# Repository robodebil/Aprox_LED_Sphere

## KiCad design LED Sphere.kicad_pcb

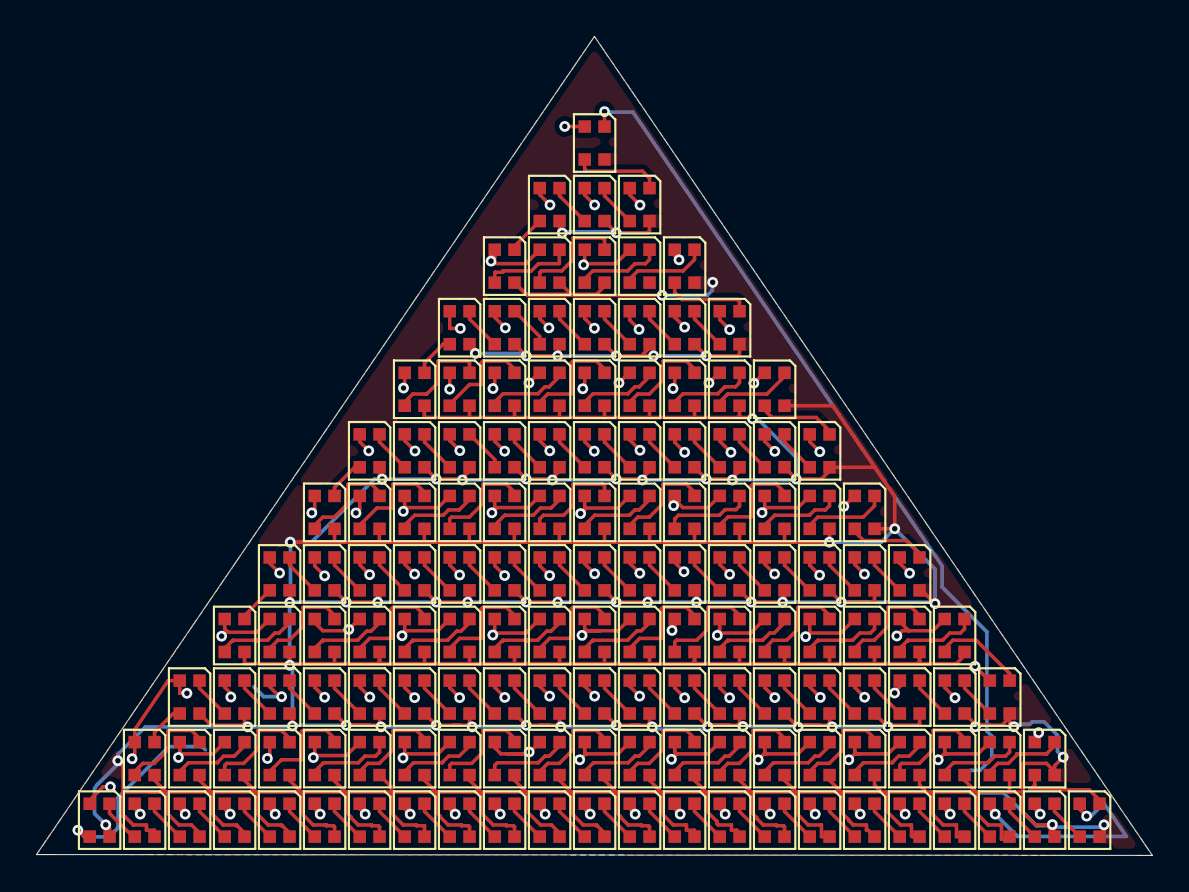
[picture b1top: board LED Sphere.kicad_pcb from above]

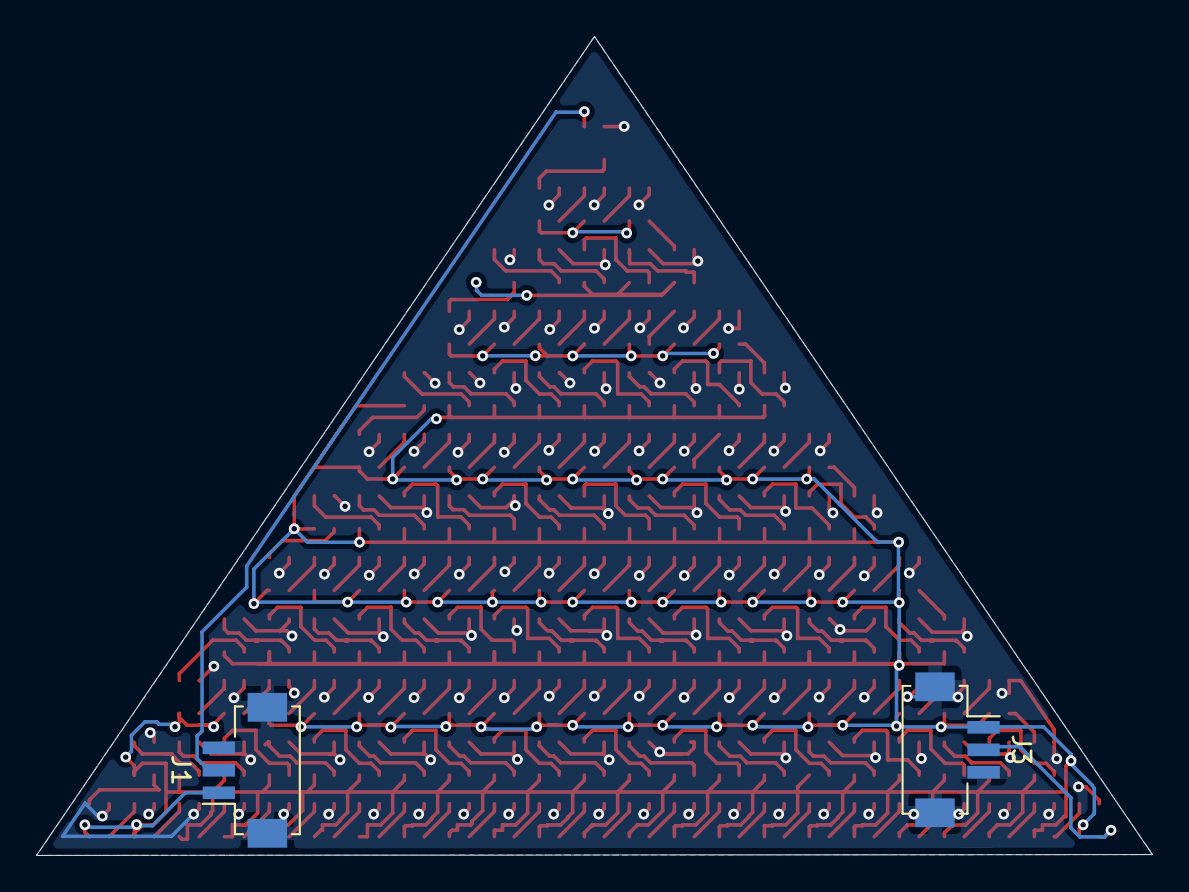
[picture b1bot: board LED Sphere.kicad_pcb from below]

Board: 2 copper layers, 62.0 x 45.5 mm, 146 parts (2 on the bottom side), 147 nets.

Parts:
D1, D2, D3, D4, D5, D6, D7, D8, D9, D10, D11, D12, D13, D14, D15, D16, D17, D18, D19, D20, D21, D22, D23, D24, D25, D26, D27, D28, D29, D30, D31, D32, D33, D34, D35, D36, D37, D38, D39, D40, D41, D42, D43, D44, D45, D46, D47, D48, D49, D50, D51, D52, D53, D54, D55, D56, D57, D58, D59, D60, D61, D62, D63, D64, D65, D66, D67, D68, D69, D70, D71, D72, D73, D74, D75, D76, D77, D78, D79, D80, D81, D82, D83, D84, D85, D86, D87, D88, D89, D90, D91, D92, D93, D94, D95, D96, D97, D98, D99, D100, D101, D102, D103, D104, D105, D106, D107, D108, D109, D110, D111, D112, D113, D114, D115, D116, D117, D118, D119, D120, D121, D122, D123, D124, D125, D126, D127, D128, D129, D130, D131, D132, D133, D134, D135, D136, D137, D138, D139, D140, D141, D142, D143, D144: WS2812B-2020; LED_WS2812B-2020_PLCC4_2.0x2.0mm
J1, J3: Conn_01x03_MountingPin; Hirose_DF13C_CL535-0403-5-51_1x03-1MP_P1.25mm_Vertical

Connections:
+5V: D1.2 (VSS), D2.2 (VSS), D3.2 (VSS), D4.2 (VSS), D5.2 (VSS), D6.2 (VSS), D7.2 (VSS), D8.2 (VSS), D9.2 (VSS), D10.2 (VSS), D11.2 (VSS), D12.2 (VSS), D13.2 (VSS), D14.2 (VSS), D15.2 (VSS), D16.2 (VSS), D17.2 (VSS), D18.2 (VSS), D19.2 (VSS), D20.2 (VSS), D21.2 (VSS), D22.2 (VSS), D23.2 (VSS), D24.2 (VSS), D25.2 (VSS), D26.2 (VSS), D27.2 (VSS), D28.2 (VSS), D29.2 (VSS), D30.2 (VSS), D31.2 (VSS), D32.2 (VSS), D33.2 (VSS), D34.2 (VSS), D35.2 (VSS), D36.2 (VSS), D37.2 (VSS), D38.2 (VSS), D39.2 (VSS), D40.2 (VSS), D41.2 (VSS), D42.2 (VSS), D43.2 (VSS), D44.2 (VSS), D45.2 (VSS), D46.2 (VSS), D47.2 (VSS), D48.2 (VSS), D49.2 (VSS), D50.2 (VSS), D51.2 (VSS), D52.2 (VSS), D53.2 (VSS), D54.2 (VSS), D55.2 (VSS), D56.2 (VSS), D57.2 (VSS), D58.2 (VSS), D59.2 (VSS), D60.2 (VSS), D61.2 (VSS), D62.2 (VSS), D63.2 (VSS), D64.2 (VSS), D65.2 (VSS), D66.2 (VSS), D67.2 (VSS), D68.2 (VSS), D69.2 (VSS), D70.2 (VSS), D71.2 (VSS), D72.2 (VSS), D73.2 (VSS), D74.2 (VSS), D75.2 (VSS), D76.2 (VSS), D77.2 (VSS), D78.2 (VSS), D79.2 (VSS), D80.2 (VSS), D81.2 (VSS), D82.2 (VSS), D83.2 (VSS), D84.2 (VSS), D85.2 (VSS), D86.2 (VSS), D87.2 (VSS), D88.2 (VSS), D89.2 (VSS), D90.2 (VSS), D91.2 (VSS), D92.2 (VSS), D93.2 (VSS), D94.2 (VSS), D95.2 (VSS), D96.2 (VSS), D97.2 (VSS), D98.2 (VSS), D99.2 (VSS), D100.2 (VSS), D101.2 (VSS), D102.2 (VSS), D103.2 (VSS), D104.2 (VSS), D105.2 (VSS), D106.2 (VSS), D107.2 (VSS), D108.2 (VSS), D109.2 (VSS), D110.2 (VSS), D111.2 (VSS), D112.2 (VSS), D113.2 (VSS), D114.2 (VSS), D115.2 (VSS), D116.2 (VSS), D117.2 (VSS), D118.2 (VSS), D119.2 (VSS), D120.2 (VSS), D121.2 (VSS), D122.2 (VSS), D123.2 (VSS), D124.2 (VSS), D125.2 (VSS), D126.2 (VSS), D127.2 (VSS), D128.2 (VSS), D129.2 (VSS), D130.2 (VSS), D131.2 (VSS), D132.2 (VSS), D133.2 (VSS), D134.2 (VSS), D135.2 (VSS), D136.2 (VSS), D137.2 (VSS), D138.2 (VSS), D139.2 (VSS), D140.2 (VSS), D141.2 (VSS), D142.2 (VSS), D143.2 (VSS), D144.2 (VSS), J1.3, J1.MP (MountPin), J3.3, J3.MP (MountPin)
/DATA_IN: D1.3 (DIN), J3.2
/DATA_OUT: D144.1 (DOUT), J1.2
GND: D1.4 (VDD), D2.4 (VDD), D3.4 (VDD), D4.4 (VDD), D5.4 (VDD), D6.4 (VDD), D7.4 (VDD), D8.4 (VDD), D9.4 (VDD), D10.4 (VDD), D11.4 (VDD), D12.4 (VDD), D13.4 (VDD), D14.4 (VDD), D15.4 (VDD), D16.4 (VDD), D17.4 (VDD), D18.4 (VDD), D19.4 (VDD), D20.4 (VDD), D21.4 (VDD), D22.4 (VDD), D23.4 (VDD), D24.4 (VDD), D25.4 (VDD), D26.4 (VDD), D27.4 (VDD), D28.4 (VDD), D29.4 (VDD), D30.4 (VDD), D31.4 (VDD), D32.4 (VDD), D33.4 (VDD), D34.4 (VDD), D35.4 (VDD), D36.4 (VDD), D37.4 (VDD), D38.4 (VDD), D39.4 (VDD), D40.4 (VDD), D41.4 (VDD), D42.4 (VDD), D43.4 (VDD), D44.4 (VDD), D45.4 (VDD), D46.4 (VDD), D47.4 (VDD), D48.4 (VDD), D49.4 (VDD), D50.4 (VDD), D51.4 (VDD), D52.4 (VDD), D53.4 (VDD), D54.4 (VDD), D55.4 (VDD), D56.4 (VDD), D57.4 (VDD), D58.4 (VDD), D59.4 (VDD), D60.4 (VDD), D61.4 (VDD), D62.4 (VDD), D63.4 (VDD), D64.4 (VDD), D65.4 (VDD), D66.4 (VDD), D67.4 (VDD), D68.4 (VDD), D69.4 (VDD), D70.4 (VDD), D71.4 (VDD), D72.4 (VDD), D73.4 (VDD), D74.4 (VDD), D75.4 (VDD), D76.4 (VDD), D77.4 (VDD), D78.4 (VDD), D79.4 (VDD), D80.4 (VDD), D81.4 (VDD), D82.4 (VDD), D83.4 (VDD), D84.4 (VDD), D85.4 (VDD), D86.4 (VDD), D87.4 (VDD), D88.4 (VDD), D89.4 (VDD), D90.4 (VDD), D91.4 (VDD), D92.4 (VDD), D93.4 (VDD), D94.4 (VDD), D95.4 (VDD), D96.4 (VDD), D97.4 (VDD), D98.4 (VDD), D99.4 (VDD), D100.4 (VDD), D101.4 (VDD), D102.4 (VDD), D103.4 (VDD), D104.4 (VDD), D105.4 (VDD), D106.4 (VDD), D107.4 (VDD), D108.4 (VDD), D109.4 (VDD), D110.4 (VDD), D111.4 (VDD), D112.4 (VDD), D113.4 (VDD), D114.4 (VDD), D115.4 (VDD), D116.4 (VDD), D117.4 (VDD), D118.4 (VDD), D119.4 (VDD), D120.4 (VDD), D121.4 (VDD), D122.4 (VDD), D123.4 (VDD), D124.4 (VDD), D125.4 (VDD), D126.4 (VDD), D127.4 (VDD), D128.4 (VDD), D129.4 (VDD), D130.4 (VDD), D131.4 (VDD), D132.4 (VDD), D133.4 (VDD), D134.4 (VDD), D135.4 (VDD), D136.4 (VDD), D138.4 (VDD), D139.4 (VDD), D140.4 (VDD), D141.4 (VDD), D142.4 (VDD), D143.4 (VDD), D144.4 (VDD), J1.1, J3.1
unnamed: D1.1 (DOUT), D2.3 (DIN)
unnamed: D2.1 (DOUT), D3.3 (DIN)
unnamed: D3.1 (DOUT), D4.3 (DIN)
unnamed: D4.1 (DOUT), D5.3 (DIN)
unnamed: D5.1 (DOUT), D6.3 (DIN)
unnamed: D6.1 (DOUT), D7.3 (DIN)
unnamed: D7.1 (DOUT), D8.3 (DIN)
unnamed: D8.1 (DOUT), D9.3 (DIN)
unnamed: D9.1 (DOUT), D10.3 (DIN)
unnamed: D10.1 (DOUT), D11.3 (DIN)
unnamed: D11.1 (DOUT), D12.3 (DIN)
unnamed: D12.1 (DOUT), D13.3 (DIN)
unnamed: D13.1 (DOUT), D14.3 (DIN)
unnamed: D14.1 (DOUT), D15.3 (DIN)
unnamed: D15.1 (DOUT), D16.3 (DIN)
unnamed: D16.1 (DOUT), D17.3 (DIN)
unnamed: D17.1 (DOUT), D18.3 (DIN)
unnamed: D18.1 (DOUT), D19.3 (DIN)
unnamed: D19.1 (DOUT), D20.3 (DIN)
unnamed: D20.1 (DOUT), D21.3 (DIN)
unnamed: D21.1 (DOUT), D22.3 (DIN)
unnamed: D22.1 (DOUT), D23.3 (DIN)
unnamed: D23.1 (DOUT), D24.3 (DIN)
unnamed: D24.1 (DOUT), D25.3 (DIN)
unnamed: D25.1 (DOUT), D26.3 (DIN)
unnamed: D26.1 (DOUT), D27.3 (DIN)
unnamed: D27.1 (DOUT), D28.3 (DIN)
unnamed: D28.1 (DOUT), D29.3 (DIN)
unnamed: D29.1 (DOUT), D30.3 (DIN)
unnamed: D30.1 (DOUT), D31.3 (DIN)
unnamed: D31.1 (DOUT), D32.3 (DIN)
unnamed: D32.1 (DOUT), D33.3 (DIN)
unnamed: D33.1 (DOUT), D34.3 (DIN)
unnamed: D34.1 (DOUT), D35.3 (DIN)
unnamed: D35.1 (DOUT), D36.3 (DIN)
unnamed: D36.1 (DOUT), D37.3 (DIN)
unnamed: D37.1 (DOUT), D38.3 (DIN)
unnamed: D38.1 (DOUT), D39.3 (DIN)
unnamed: D39.1 (DOUT), D40.3 (DIN)
unnamed: D40.1 (DOUT), D41.3 (DIN)
unnamed: D41.1 (DOUT), D42.3 (DIN)
unnamed: D42.1 (DOUT), D43.3 (DIN)
unnamed: D43.1 (DOUT), D44.3 (DIN)
unnamed: D44.1 (DOUT), D45.3 (DIN)
unnamed: D45.1 (DOUT), D46.3 (DIN)
unnamed: D46.1 (DOUT), D47.3 (DIN)
unnamed: D47.1 (DOUT), D48.3 (DIN)
unnamed: D48.1 (DOUT), D49.3 (DIN)
unnamed: D49.1 (DOUT), D50.3 (DIN)
unnamed: D50.1 (DOUT), D51.3 (DIN)
unnamed: D51.1 (DOUT), D52.3 (DIN)
unnamed: D52.1 (DOUT), D53.3 (DIN)
unnamed: D53.1 (DOUT), D54.3 (DIN)
unnamed: D54.1 (DOUT), D55.3 (DIN)
unnamed: D55.1 (DOUT), D56.3 (DIN)
unnamed: D56.1 (DOUT), D57.3 (DIN)
unnamed: D57.1 (DOUT), D58.3 (DIN)
unnamed: D58.1 (DOUT), D59.3 (DIN)
unnamed: D59.1 (DOUT), D60.3 (DIN)
unnamed: D60.1 (DOUT), D61.3 (DIN)
unnamed: D61.1 (DOUT), D62.3 (DIN)
unnamed: D62.1 (DOUT), D63.3 (DIN)
unnamed: D63.1 (DOUT), D64.3 (DIN)
unnamed: D64.1 (DOUT), D65.3 (DIN)
unnamed: D65.1 (DOUT), D66.3 (DIN)
unnamed: D66.1 (DOUT), D67.3 (DIN)
unnamed: D67.1 (DOUT), D68.3 (DIN)
unnamed: D68.1 (DOUT), D69.3 (DIN)
unnamed: D69.1 (DOUT), D70.3 (DIN)
unnamed: D70.1 (DOUT), D71.3 (DIN)
unnamed: D71.1 (DOUT), D72.3 (DIN)
unnamed: D72.1 (DOUT), D73.3 (DIN)
unnamed: D73.1 (DOUT), D74.3 (DIN)
unnamed: D74.1 (DOUT), D75.3 (DIN)
unnamed: D75.1 (DOUT), D76.3 (DIN)
unnamed: D76.1 (DOUT), D77.3 (DIN)
unnamed: D77.1 (DOUT), D78.3 (DIN)
unnamed: D78.1 (DOUT), D79.3 (DIN)
unnamed: D79.1 (DOUT), D80.3 (DIN)
unnamed: D80.1 (DOUT), D81.3 (DIN)
unnamed: D81.1 (DOUT), D82.3 (DIN)
unnamed: D82.1 (DOUT), D83.3 (DIN)
unnamed: D83.1 (DOUT), D84.3 (DIN)
unnamed: D84.1 (DOUT), D85.3 (DIN)
unnamed: D85.1 (DOUT), D86.3 (DIN)
unnamed: D86.1 (DOUT), D87.3 (DIN)
unnamed: D87.1 (DOUT), D88.3 (DIN)
unnamed: D88.1 (DOUT), D89.3 (DIN)
unnamed: D89.1 (DOUT), D90.3 (DIN)
unnamed: D90.1 (DOUT), D91.3 (DIN)
unnamed: D91.1 (DOUT), D92.3 (DIN)
unnamed: D92.1 (DOUT), D93.3 (DIN)
unnamed: D93.1 (DOUT), D94.3 (DIN)
unnamed: D94.1 (DOUT), D95.3 (DIN)
unnamed: D95.1 (DOUT), D96.3 (DIN)
unnamed: D96.1 (DOUT), D97.3 (DIN)
unnamed: D97.1 (DOUT), D98.3 (DIN)
unnamed: D98.1 (DOUT), D99.3 (DIN)
unnamed: D99.1 (DOUT), D100.3 (DIN)
unnamed: D100.1 (DOUT), D101.3 (DIN)
unnamed: D101.1 (DOUT), D102.3 (DIN)
unnamed: D102.1 (DOUT), D103.3 (DIN)
unnamed: D103.1 (DOUT), D104.3 (DIN)
unnamed: D104.1 (DOUT), D105.3 (DIN)
unnamed: D105.1 (DOUT), D106.3 (DIN)
unnamed: D106.1 (DOUT), D107.3 (DIN)
unnamed: D107.1 (DOUT), D108.3 (DIN)
unnamed: D108.1 (DOUT), D109.3 (DIN)
unnamed: D109.1 (DOUT), D110.3 (DIN)
unnamed: D110.1 (DOUT), D111.3 (DIN)
unnamed: D111.1 (DOUT), D112.3 (DIN)
unnamed: D112.1 (DOUT), D113.3 (DIN)
unnamed: D113.1 (DOUT), D114.3 (DIN)
unnamed: D114.1 (DOUT), D115.3 (DIN)
unnamed: D115.1 (DOUT), D116.3 (DIN)
unnamed: D116.1 (DOUT), D117.3 (DIN)
unnamed: D117.1 (DOUT), D118.3 (DIN)
unnamed: D118.1 (DOUT), D119.3 (DIN)
unnamed: D119.1 (DOUT), D120.3 (DIN)
unnamed: D120.1 (DOUT), D121.3 (DIN)
unnamed: D121.1 (DOUT), D122.3 (DIN)
unnamed: D122.1 (DOUT), D123.3 (DIN)
unnamed: D123.1 (DOUT), D124.3 (DIN)
unnamed: D124.1 (DOUT), D125.3 (DIN)
unnamed: D125.1 (DOUT), D126.3 (DIN)
unnamed: D126.1 (DOUT), D127.3 (DIN)
unnamed: D127.1 (DOUT), D128.3 (DIN)
unnamed: D128.1 (DOUT), D129.3 (DIN)
unnamed: D129.1 (DOUT), D130.3 (DIN)
unnamed: D130.1 (DOUT), D131.3 (DIN)
unnamed: D131.1 (DOUT), D132.3 (DIN)
unnamed: D132.1 (DOUT), D133.3 (DIN)
unnamed: D133.1 (DOUT), D134.3 (DIN)
unnamed: D134.1 (DOUT), D135.3 (DIN)
unnamed: D135.1 (DOUT), D136.3 (DIN)
unnamed: D136.1 (DOUT), D137.3 (DIN)
unnamed: D137.1 (DOUT), D138.3 (DIN)
unnamed: D138.1 (DOUT), D139.3 (DIN)
unnamed: D139.1 (DOUT), D140.3 (DIN)
unnamed: D140.1 (DOUT), D141.3 (DIN)
unnamed: D141.1 (DOUT), D142.3 (DIN)
unnamed: D142.1 (DOUT), D143.3 (DIN)
unnamed: D143.1 (DOUT), D144.3 (DIN)

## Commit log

2026-04-04 main
